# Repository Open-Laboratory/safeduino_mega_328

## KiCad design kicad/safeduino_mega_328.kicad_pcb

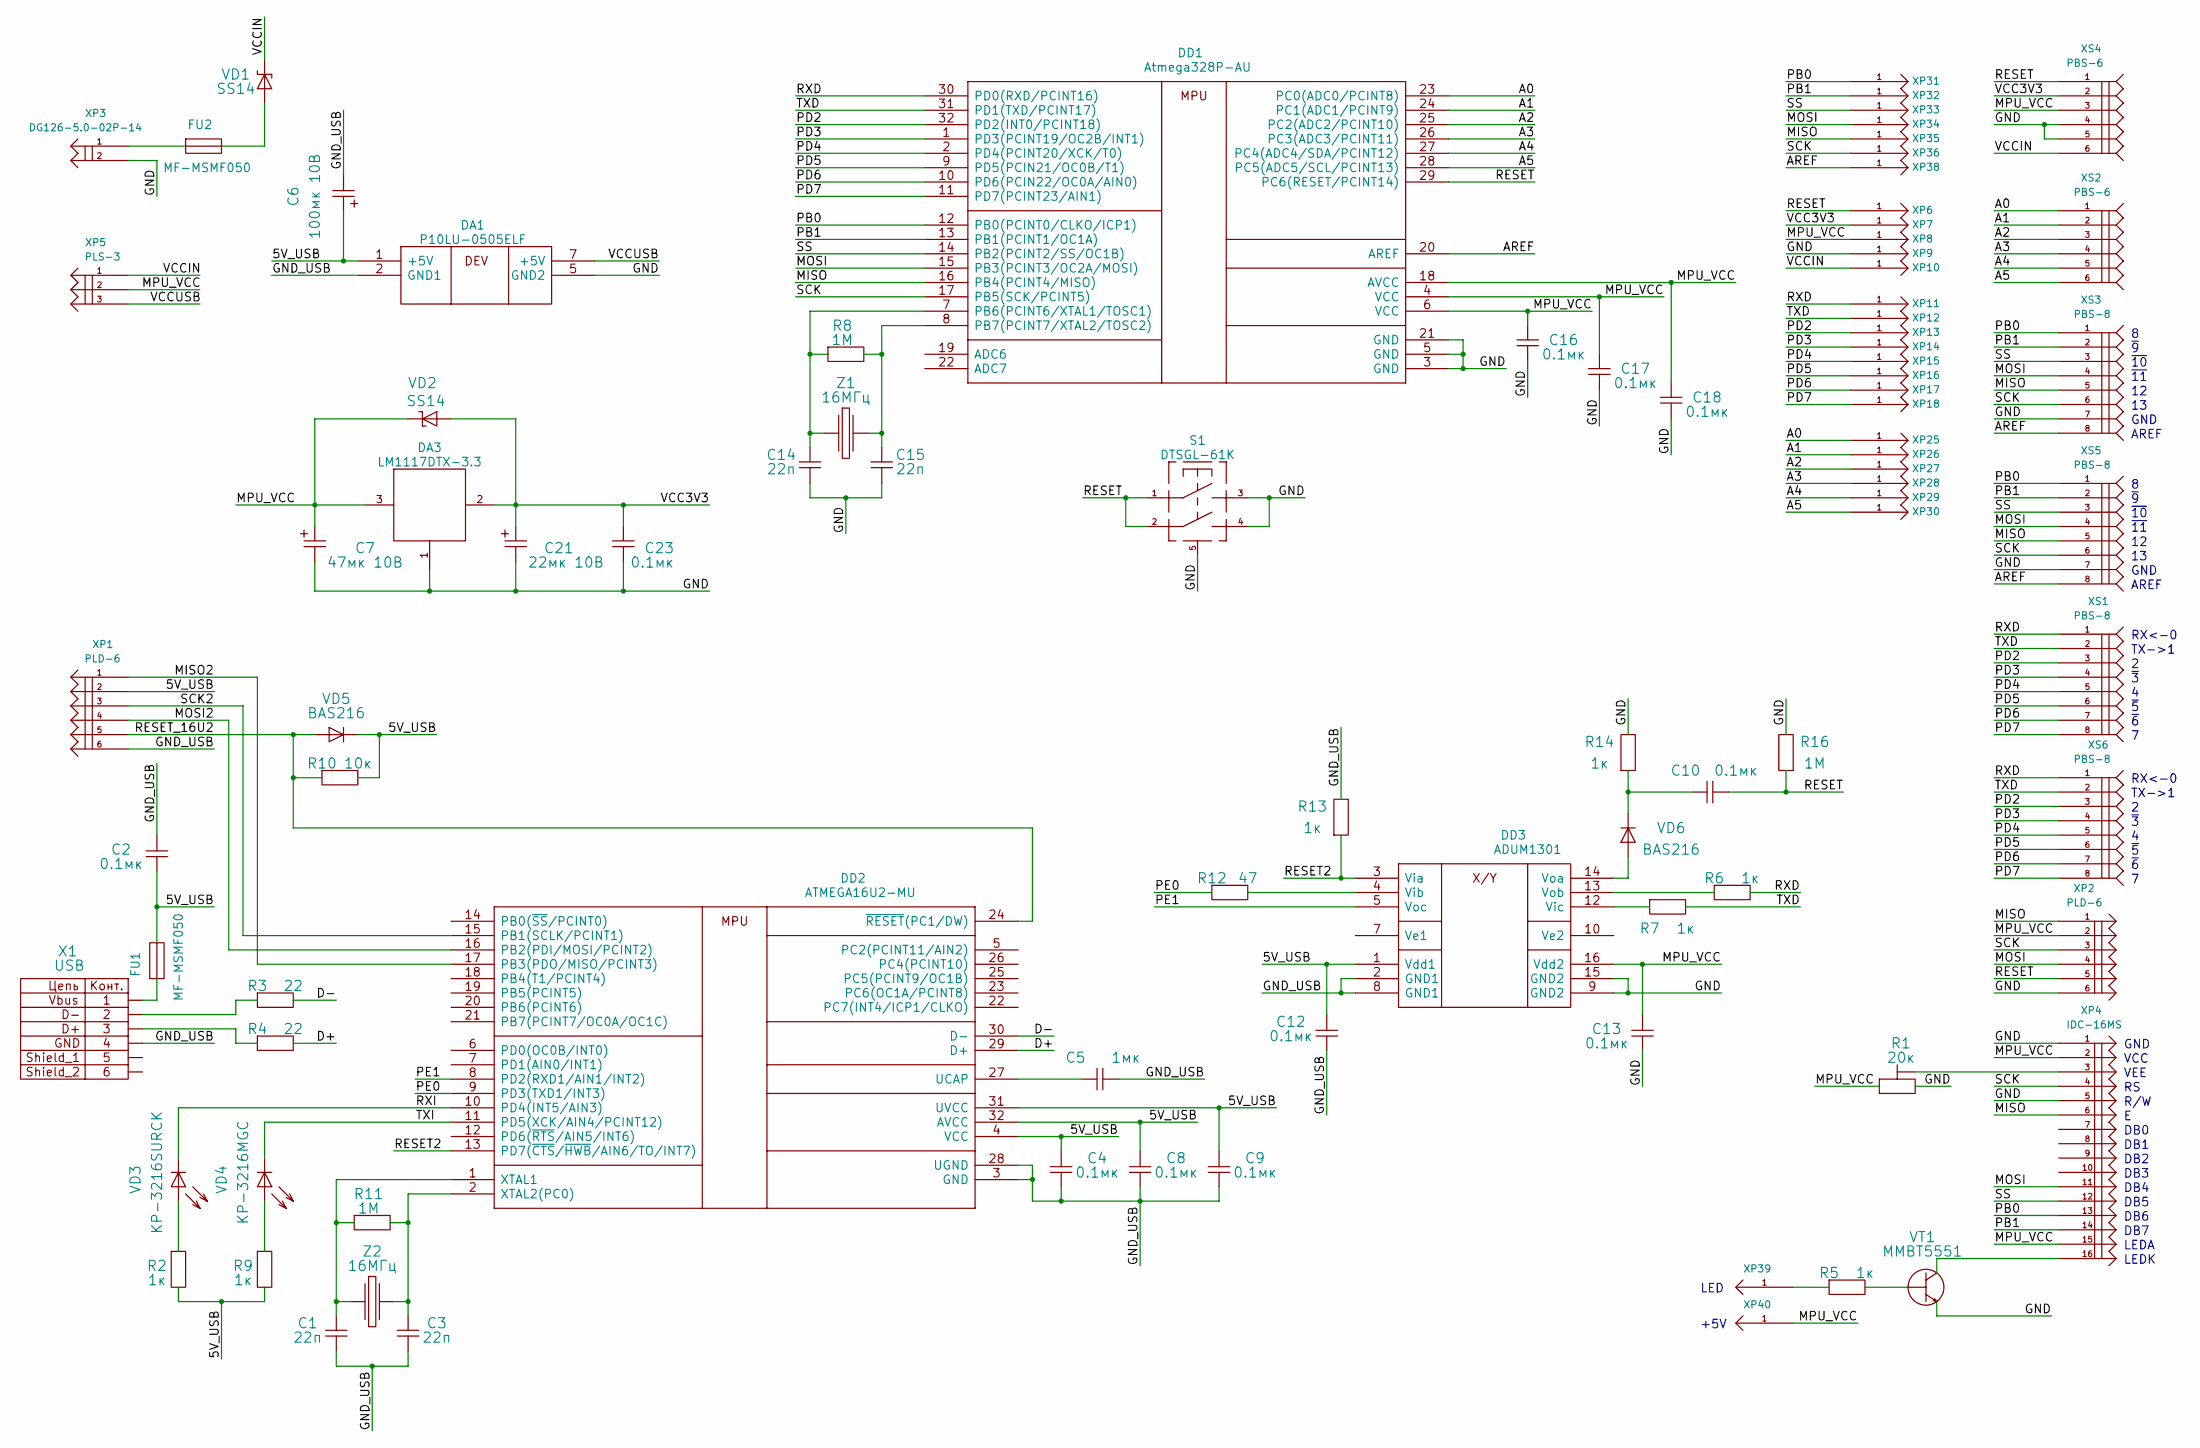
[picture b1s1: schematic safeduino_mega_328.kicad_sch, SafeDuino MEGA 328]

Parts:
C1, C3, C14, C15: 22п
C2, C4, C8, C9, C10, C12, C13, C16, C17, C18, C23: 0.1мк
C5: 1мк
C6: 100мк 10В
C7: 47мк 10В
C21: 22мк 10В
DA1: P10LU-0505ELF
DA3: LM1117DTX-3.3
DD1: Atmega328P-AU
DD2: ATMEGA16U2-MU
DD3: ADUM1301
FU1, FU2: MF-MSMF050
R1: 20к
R2, R5, R6, R7, R9, R13, R14: 1к
R3, R4: 22
R8, R11, R16: 1M
R10: 10к
R12: 47
S1: DTSGL-61K
VD1, VD2: SS14
VD3: KP-3216SURCK
VD4: KP-3216MGC
VD5, VD6: BAS216
VT1: MMBT5551
X1: USB
XP1, XP2: PLD-6
XP3: DG126-5.0-02P-14
XP4: IDC-16MS
XP5: PLS-3
XP6, XP7, XP8, XP9, XP10, XP11, XP12, XP13, XP14, XP15, XP16, XP17, XP18, XP25, XP26, XP27, XP28, XP29, XP30, XP31, XP32, XP33, XP34, XP35, XP36, XP38, XP39, XP40: (no value)
XS1, XS3, XS5, XS6: PBS-8
XS2, XS4: PBS-6
Z1, Z2: 16МГц

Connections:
/5V_USB: C2.1, C4.2, C6.1, C8.2, C9.2, C12.2, DA1.1 (+5V), DD2.4 (VCC), DD2.31 (UVCC), DD2.32 (AVCC), DD3.1 (Vdd1), FU1.2, R2.2, R9.2, R10.2, VD5.2, XP1.2
/A0: DD1.23 (PC0(ADC0/PCINT8)), XP25.1, XS2.1
/A1: DD1.24 (PC1(ADC1/PCINT9)), XP26.1, XS2.2
/A2: DD1.25 (PC2(ADC2/PCINT10)), XP27.1, XS2.3
/A3: DD1.26 (PC3(ADC3/PCINT11)), XP28.1, XS2.4
/A4: DD1.27 (PC4(ADC4/SDA/PCINT12)), XP29.1, XS2.5
/A5: DD1.28 (PC5(ADC5/SCL/PCINT13)), XP30.1, XS2.6
/AREF: DD1.20 (AREF), XP38.1, XS3.8, XS5.8
/D+: DD2.29 (D+), R4.2
/D-: DD2.30 (D-), R3.2
/GND: C7.2, C13.1, C14.2, C15.2, C16.2, C17.2, C18.2, C21.2, C23.2, DA1.5 (GND2), DA3.1 (com), DD1.3 (GND), DD1.5 (GND), DD1.21 (GND), DD3.9 (GND2), DD3.15 (GND2), R1.3, R14.2, R16.2, S1.3, S1.4, S1.5, VT1.1, XP2.6, XP3.2, XP4.1, XP4.5, XP9.1, XS3.7, XS4.4, XS4.5, XS5.7
/GND_USB: C1.2, C2.2, C3.2, C4.1, C5.2, C6.2, C8.1, C9.1, C12.1, DA1.2 (GND1), DD2.3 (GND), DD2.28 (UGND), DD3.2 (GND1), DD3.8 (GND1), R13.2, X1.4 (GND), XP1.6
/MISO: DD1.16 (PB4(PCINT4/MISO)), XP2.1, XP4.6, XP35.1, XS3.5, XS5.5
/MISO2: DD2.17 (PB3(PDO/MISO/PCINT3)), XP1.1
/MOSI: DD1.15 (PB3(PCINT3/OC2A/MOSI)), XP2.4, XP4.11, XP34.1, XS3.4, XS5.4
/MOSI2: DD2.16 (PB2(PDI/MOSI/PCINT2)), XP1.4
/MPU_VCC: C7.1, C13.2, C16.1, C17.1, C18.1, DA3.3 (Vin), DD1.4 (VCC), DD1.6 (VCC), DD1.18 (AVCC), DD3.16 (Vdd2), R1.1, VD2.2, XP2.2, XP4.2, XP4.15, XP5.2, XP8.1, XP40.1, XS4.3
/PB0: DD1.12 (PB0(PCINT0/CLKO/ICP1)), XP4.13, XP31.1, XS3.1, XS5.1
/PB1: DD1.13 (PB1(PCINT1/OC1A)), XP4.14, XP32.1, XS3.2, XS5.2
/PD2: DD1.32 (PD2(INT0/PCINT18)), XP13.1, XS1.3, XS6.3
/PD3: DD1.1 (PD3(PCINT19/OC2B/INT1)), XP14.1, XS1.4, XS6.4
/PD4: DD1.2 (PD4(PCINT20/XCK/T0)), XP15.1, XS1.5, XS6.5
/PD5: DD1.9 (PD5(PCIN21/OC0B/T1)), XP16.1, XS1.6, XS6.6
/PD6: DD1.10 (PD6(PCIN22/OC0A/AIN0)), XP17.1, XS1.7, XS6.7
/PD7: DD1.11 (PD7(PCINT23/AIN1)), XP18.1, XS1.8, XS6.8
/PE0: DD2.9 (PD3(TXD1/INT3)), R12.1
/PE1: DD2.8 (PD2(RXD1/AIN1/INT2)), DD3.5 (Voc)
/RESET: C10.2, DD1.29 (PC6(RESET/PCINT14)), R16.1, S1.1, S1.2, XP2.5, XP6.1, XS4.1
/RESET2: DD2.13 (PD7(~CTS/~HWB/AIN6/TO/INT7)), DD3.3 (Via), R13.1
/RESET_16U2: DD2.24 (~RESET(PC1/DW)), R10.1, VD5.1, XP1.5
/RXD: DD1.30 (PD0(RXD/PCINT16)), R6.2, XP11.1, XS1.1, XS6.1
/RXI: DD2.10 (PD4(INT5/AIN3)), VD3.2
/SCK: DD1.17 (PB5(SCK/PCINT5)), XP2.3, XP4.4, XP36.1, XS3.6, XS5.6
/SCK2: DD2.15 (PB1(SCLK/PCINT1)), XP1.3
/SS: DD1.14 (PB2(PCINT2/SS/OC1B)), XP4.12, XP33.1, XS3.3, XS5.3
/TXD: DD1.31 (PD1(TXD/PCINT17)), R7.2, XP12.1, XS1.2, XS6.2
/TXI: DD2.11 (PD5(XCK/AIN4/PCINT12)), VD4.2
/VCC3V3: C21.1, C23.1, DA3.2 (Vout), VD2.1, XP7.1, XS4.2
/VCCIN: VD1.2, XP5.1, XP10.1, XS4.6
/VCCUSB: DA1.7 (+5V), XP5.3
unnamed: C1.1, DD2.1 (XTAL1), R11.1, Z2.1
unnamed: C3.1, DD2.2 (XTAL2(PC0)), R11.2, Z2.2
unnamed: C5.1, DD2.27 (UCAP)
unnamed: C10.1, R14.1, VD6.2
unnamed: C14.1, DD1.7 (PB6(PCINT6/XTAL1/TOSC1)), R8.1, Z1.1
unnamed: C15.1, DD1.8 (PB7(PCINT7/XTAL2/TOSC2)), R8.2, Z1.2
unnamed: DD3.4 (Vib), R12.2
unnamed: DD3.12 (Vic), R7.1
unnamed: DD3.13 (Vob), R6.1
unnamed: DD3.14 (Voa), VD6.1
unnamed: FU1.1, X1.1 (Vbus)
unnamed: FU2.1, XP3.1
unnamed: FU2.2, VD1.1
unnamed: R1.2, XP4.3
unnamed: R2.1, VD3.1
unnamed: R3.1, X1.2 (D-)
unnamed: R4.1, X1.3 (D+)
unnamed: R5.1, XP39.1
unnamed: R5.2, VT1.2
unnamed: R9.1, VD4.1
unnamed: VT1.3, XP4.16

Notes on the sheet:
GND
RX<-0
DB2
AREF
TX->1
~{3}
DB6
DB5
~{6}
LEDA
DB7
LED
~{5}
VEE
DB3
~{10}
~{9}
DB1
~{11}
LEDK
+5V
R/W
DB4
VCC
DB0

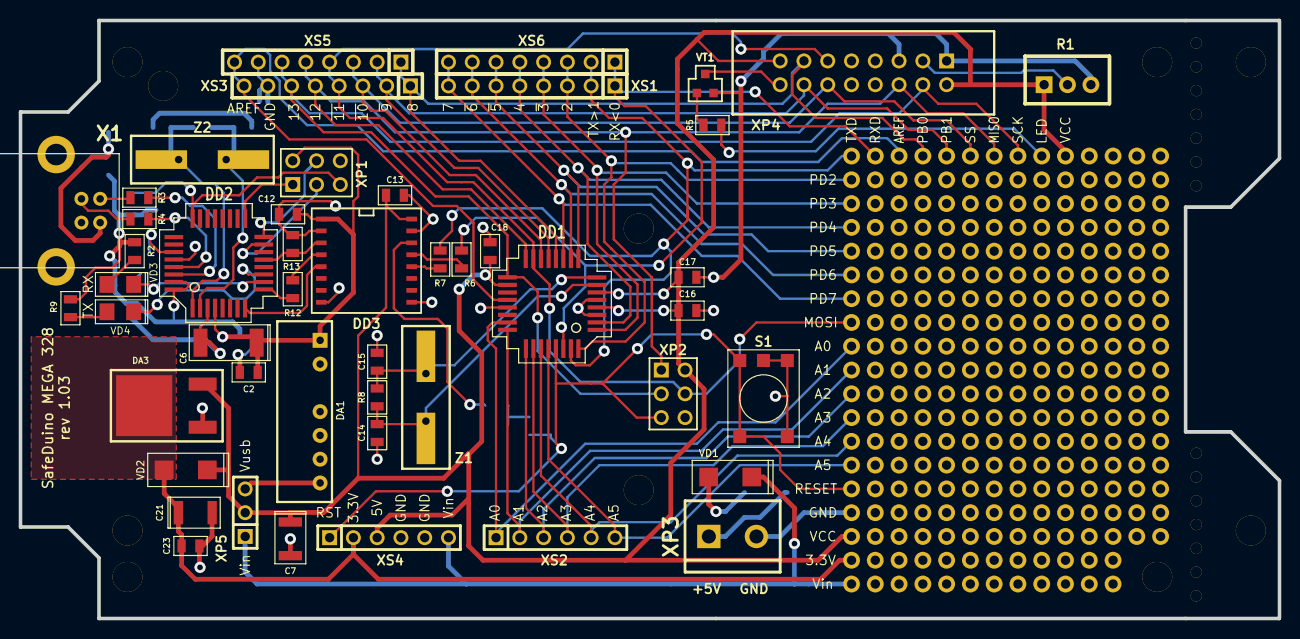
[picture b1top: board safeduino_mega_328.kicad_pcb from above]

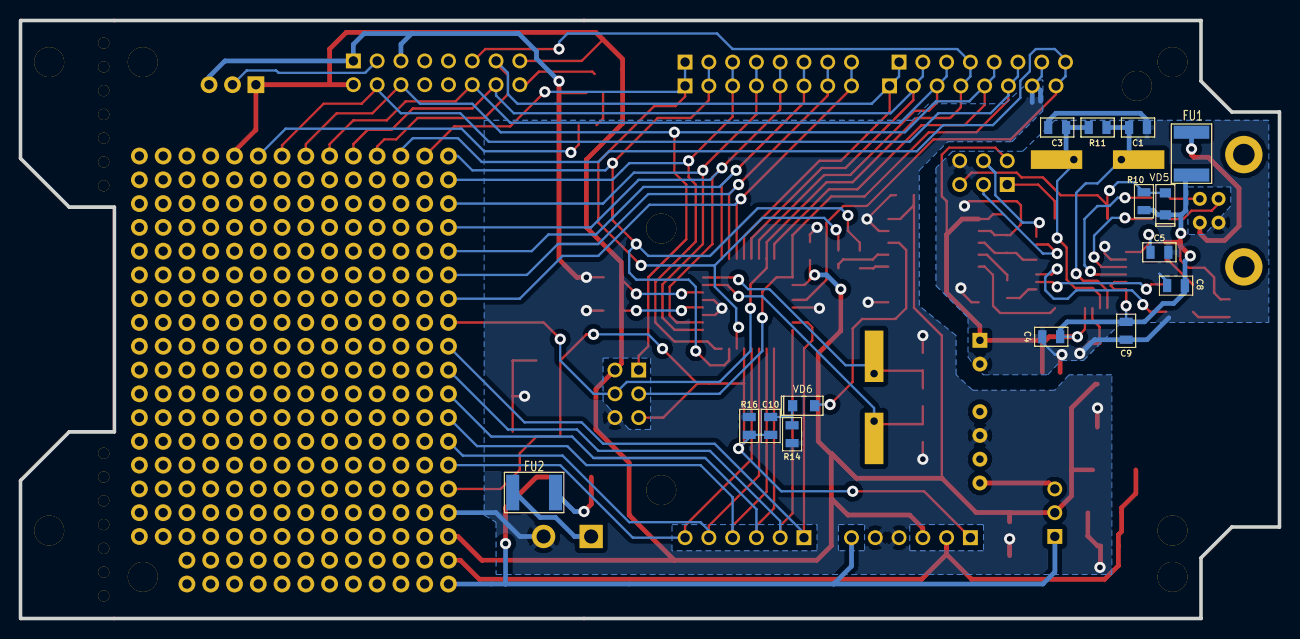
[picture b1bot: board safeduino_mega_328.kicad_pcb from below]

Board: 2 copper layers, 134.5 x 63.9 mm, 101 parts (15 on the bottom side), 61 nets.

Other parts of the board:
G447, G447#2, G447#3, G762/G447/HB11460: P***; 1_pin
HB11460/G762, HB11460/G762#2, HB11460/G762/arduino: P***; 1_pin
arduino: P***; 1_pin
arduino#2, arduino#3: P***; 1_pin

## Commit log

2016-02-19 Заменил FTDI на Atmega16u2.
2016-02-19 Начал переразводить печатную плату.
2016-02-20 Закончил разводку платы.
2016-02-24 Добавил самовостанавливающиеся предохренители на 0.5А.
2016-03-10 Заменил резистор R15 на диод VD6 для защиты ADUM от попадания напряжения.
2016-05-23 SafeDuino MEGA 328 v1.02 полностью готова к отправке на изготовление.
2016-07-13 Исправли ошибку на плате SafeDuino MEGA 328(был не соединён контакт PE0 на плате).
2018-07-20 Поправил шелкографию на плате.
2023-07-11 Перевёл проект на Kicad 6.0.
